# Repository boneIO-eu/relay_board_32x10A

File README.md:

# relay_board_32x10A
Realy Board 32x10A

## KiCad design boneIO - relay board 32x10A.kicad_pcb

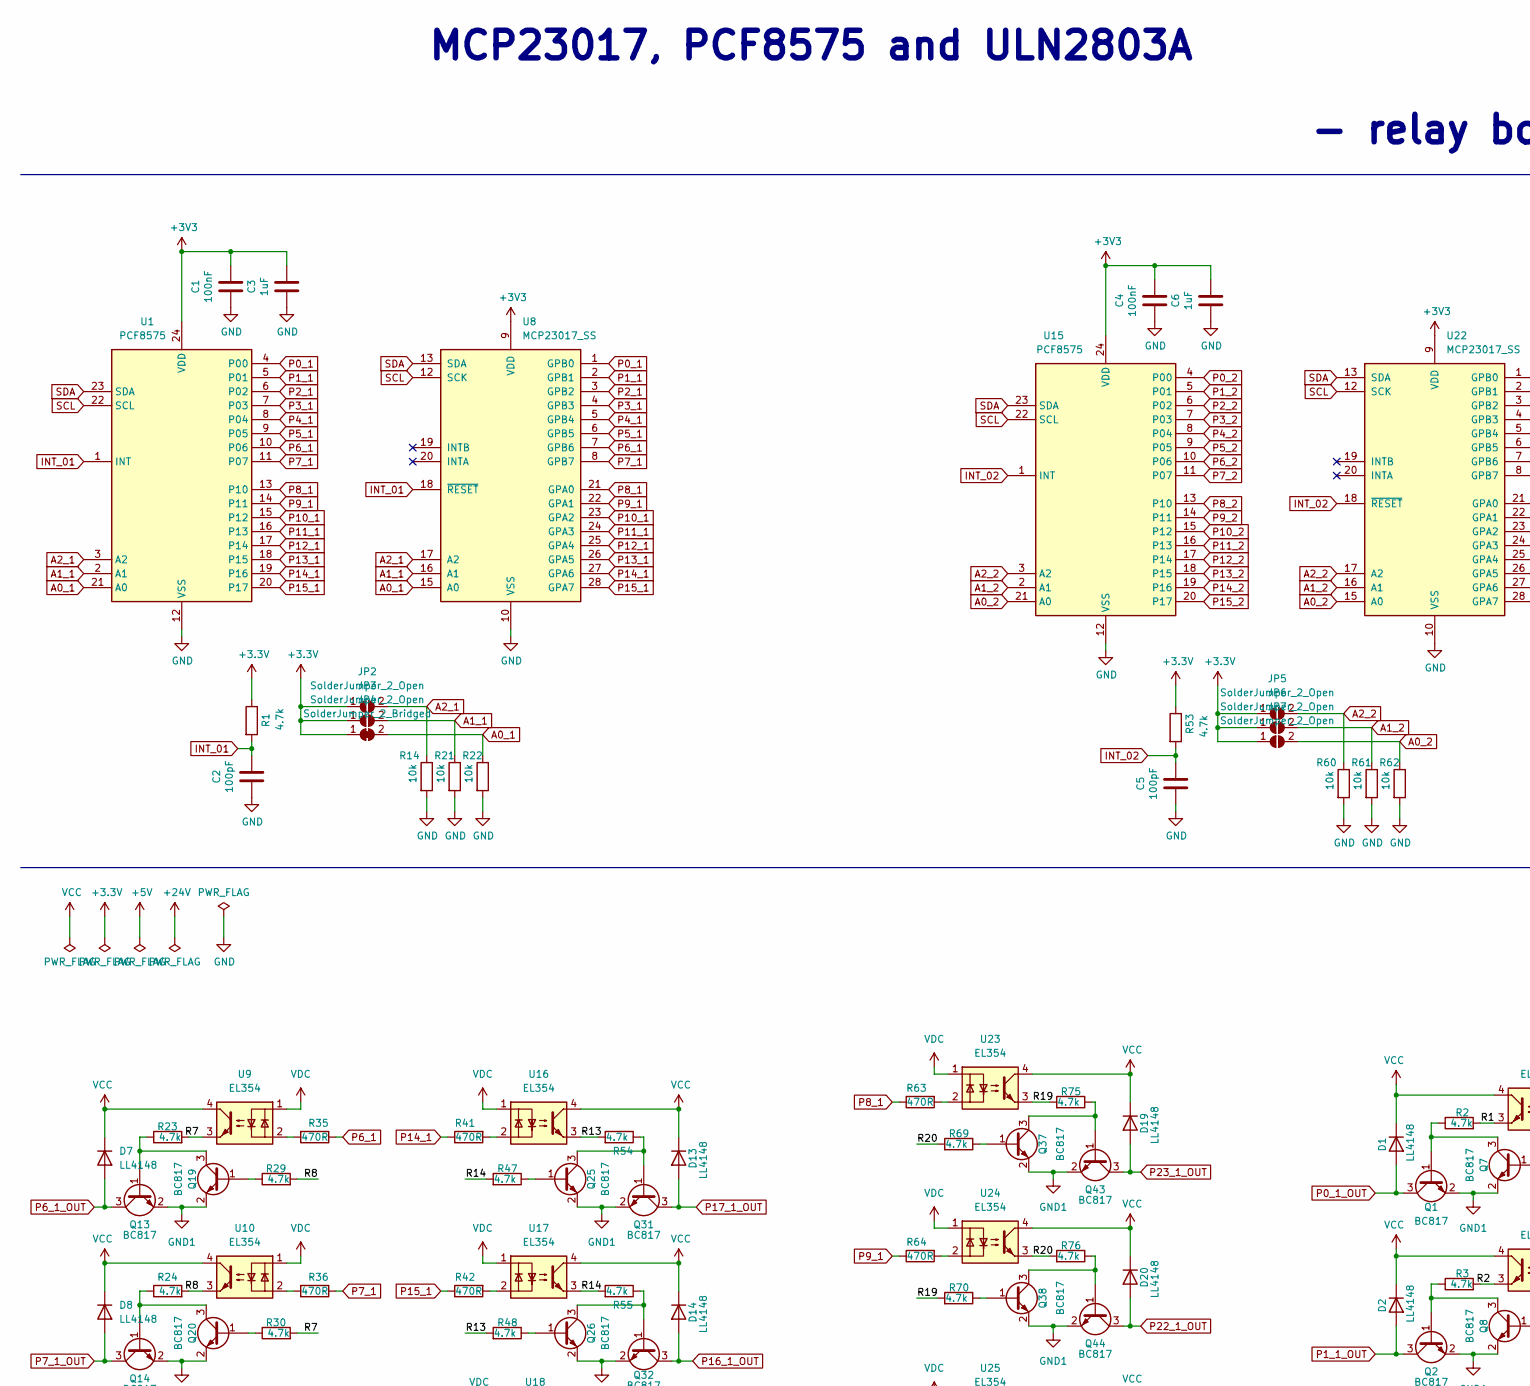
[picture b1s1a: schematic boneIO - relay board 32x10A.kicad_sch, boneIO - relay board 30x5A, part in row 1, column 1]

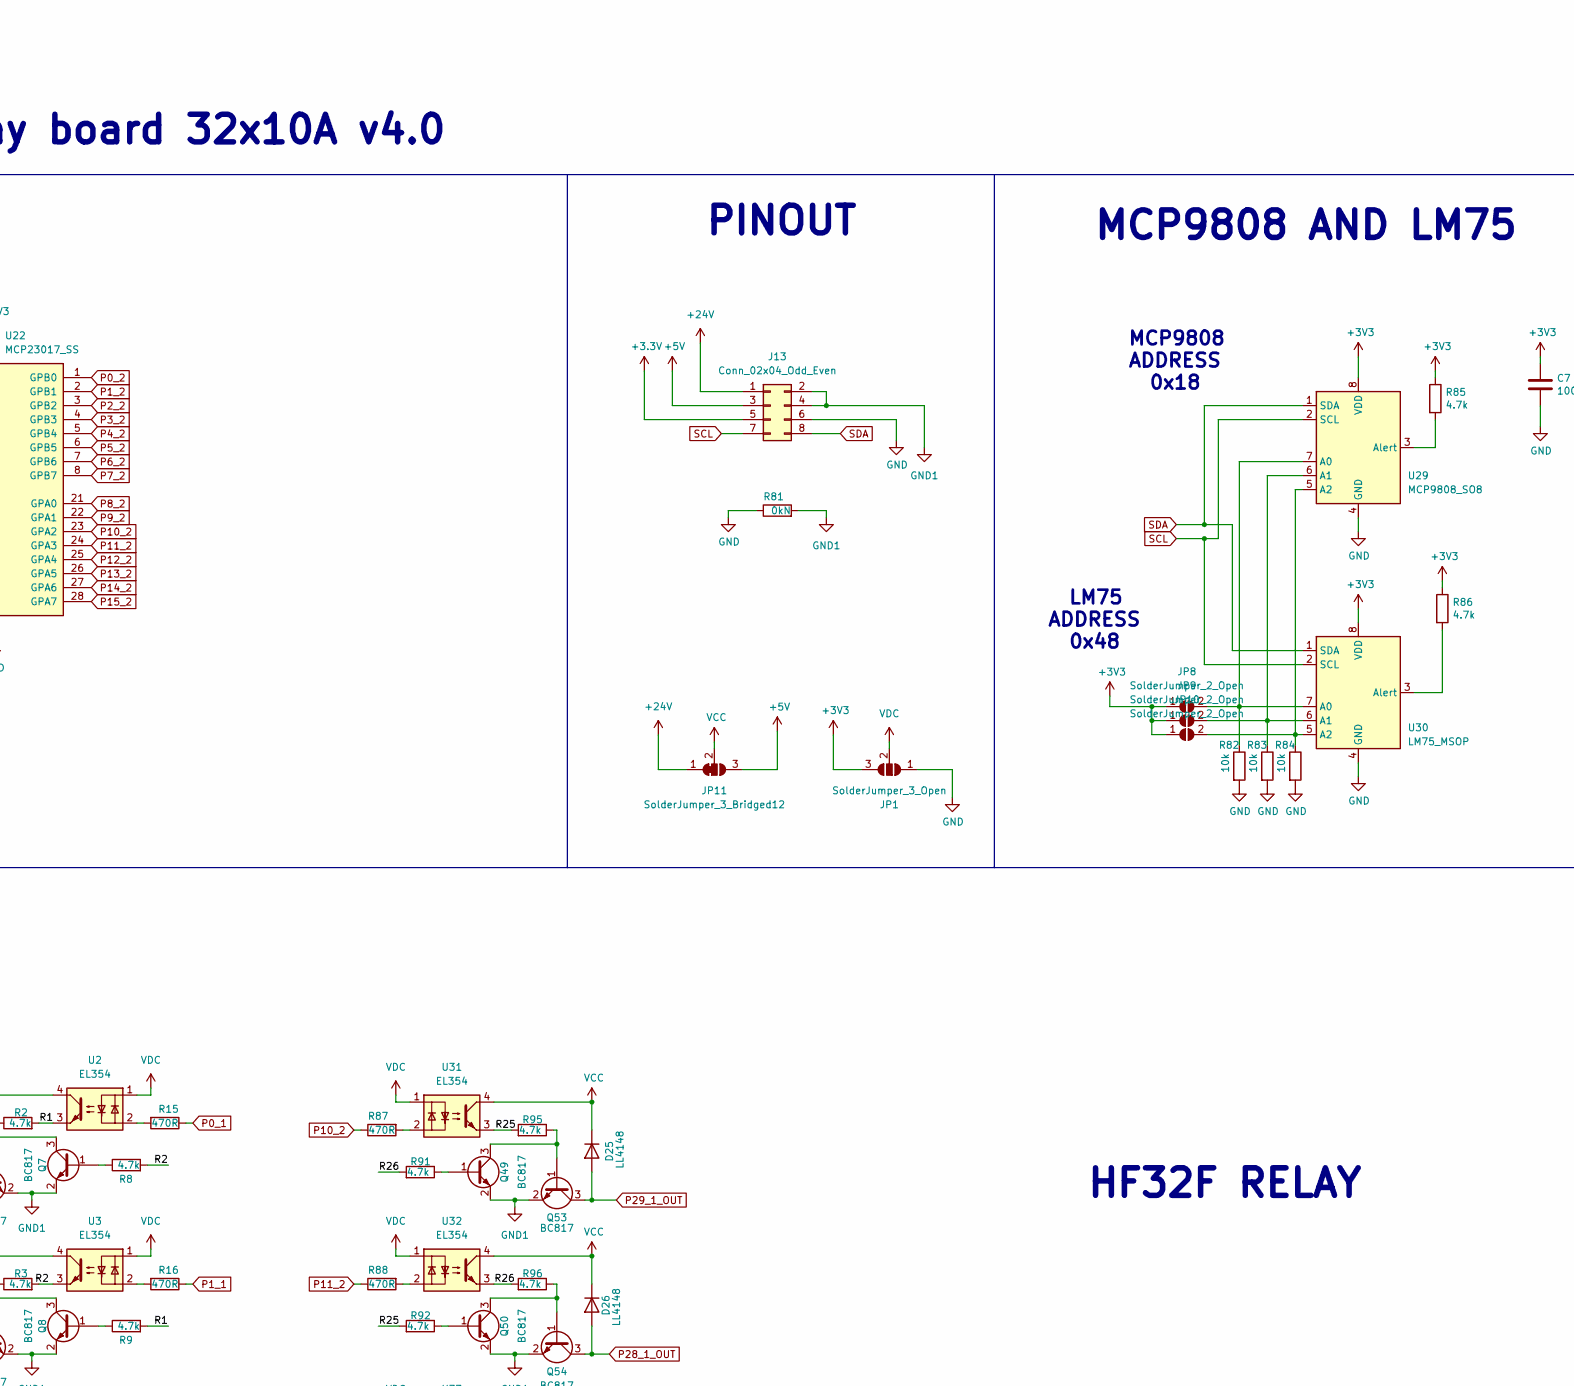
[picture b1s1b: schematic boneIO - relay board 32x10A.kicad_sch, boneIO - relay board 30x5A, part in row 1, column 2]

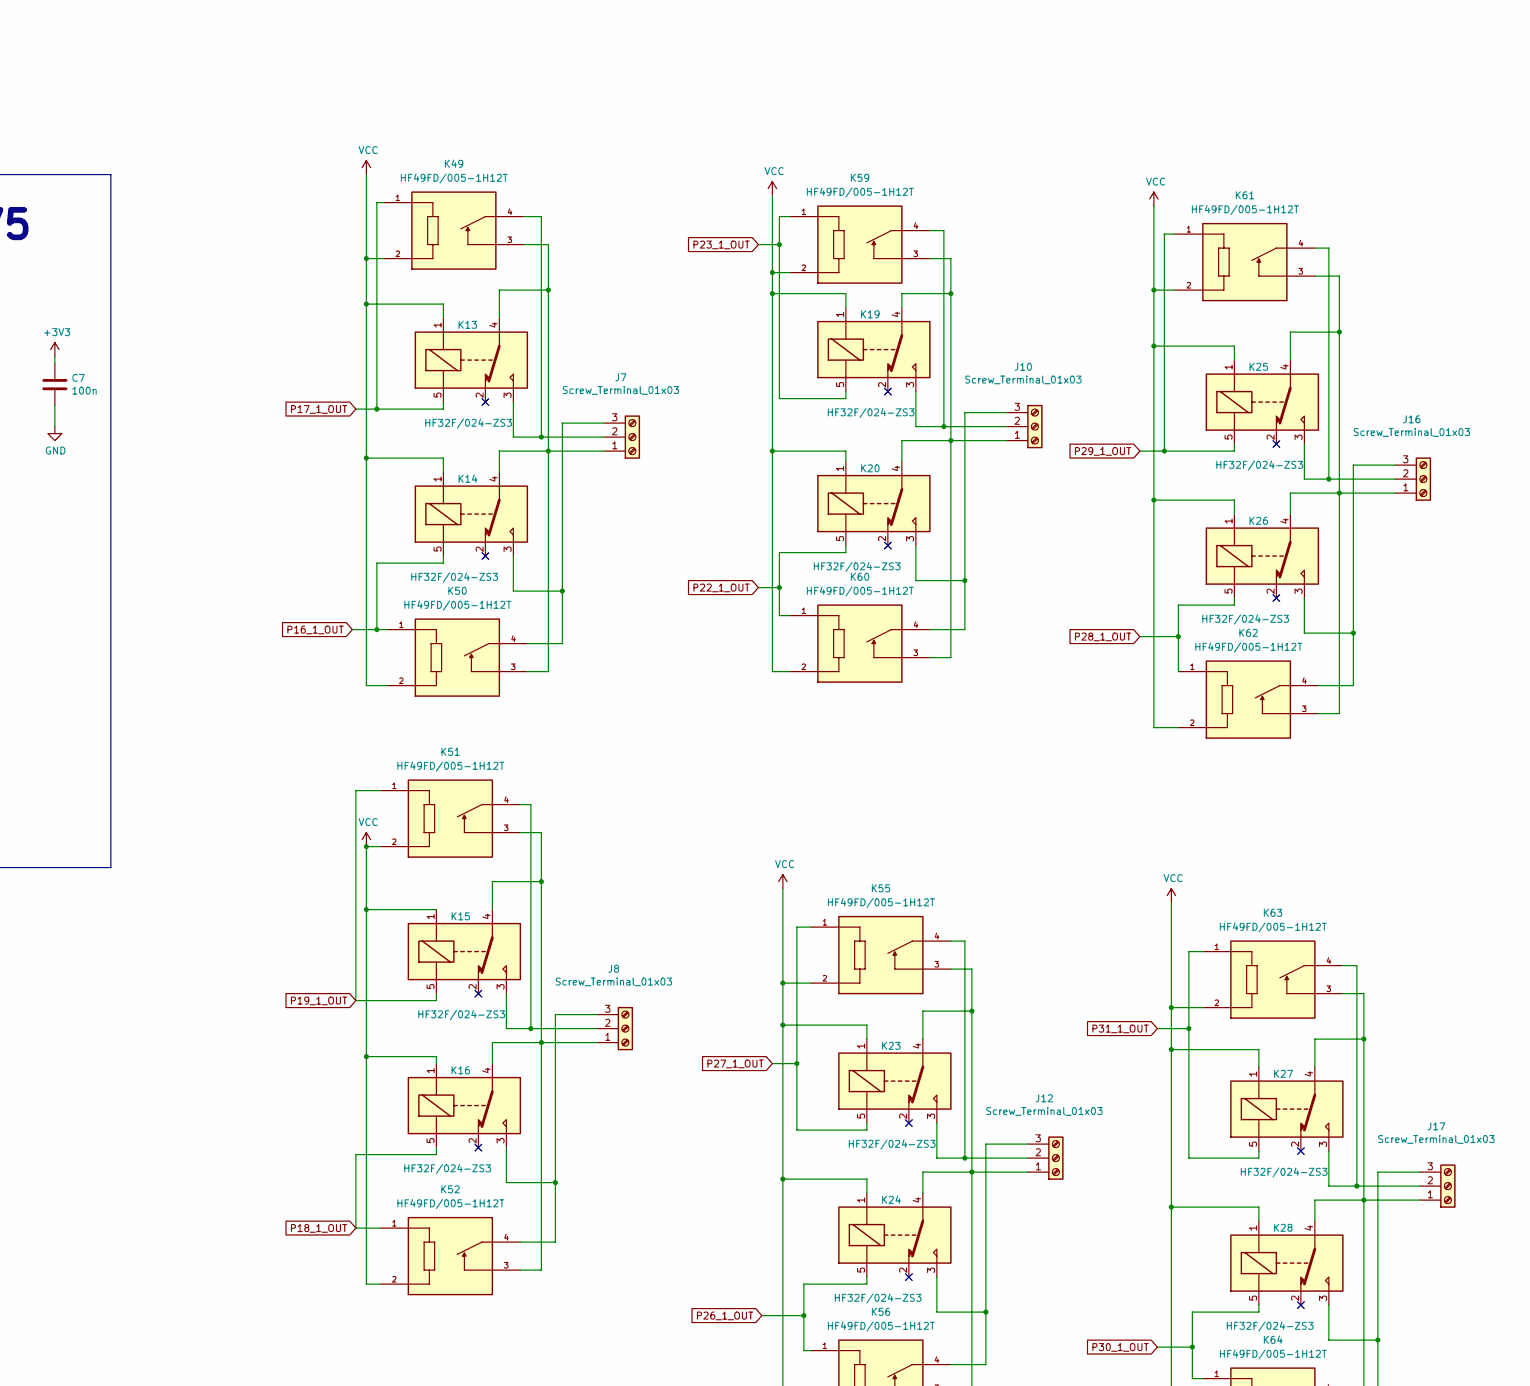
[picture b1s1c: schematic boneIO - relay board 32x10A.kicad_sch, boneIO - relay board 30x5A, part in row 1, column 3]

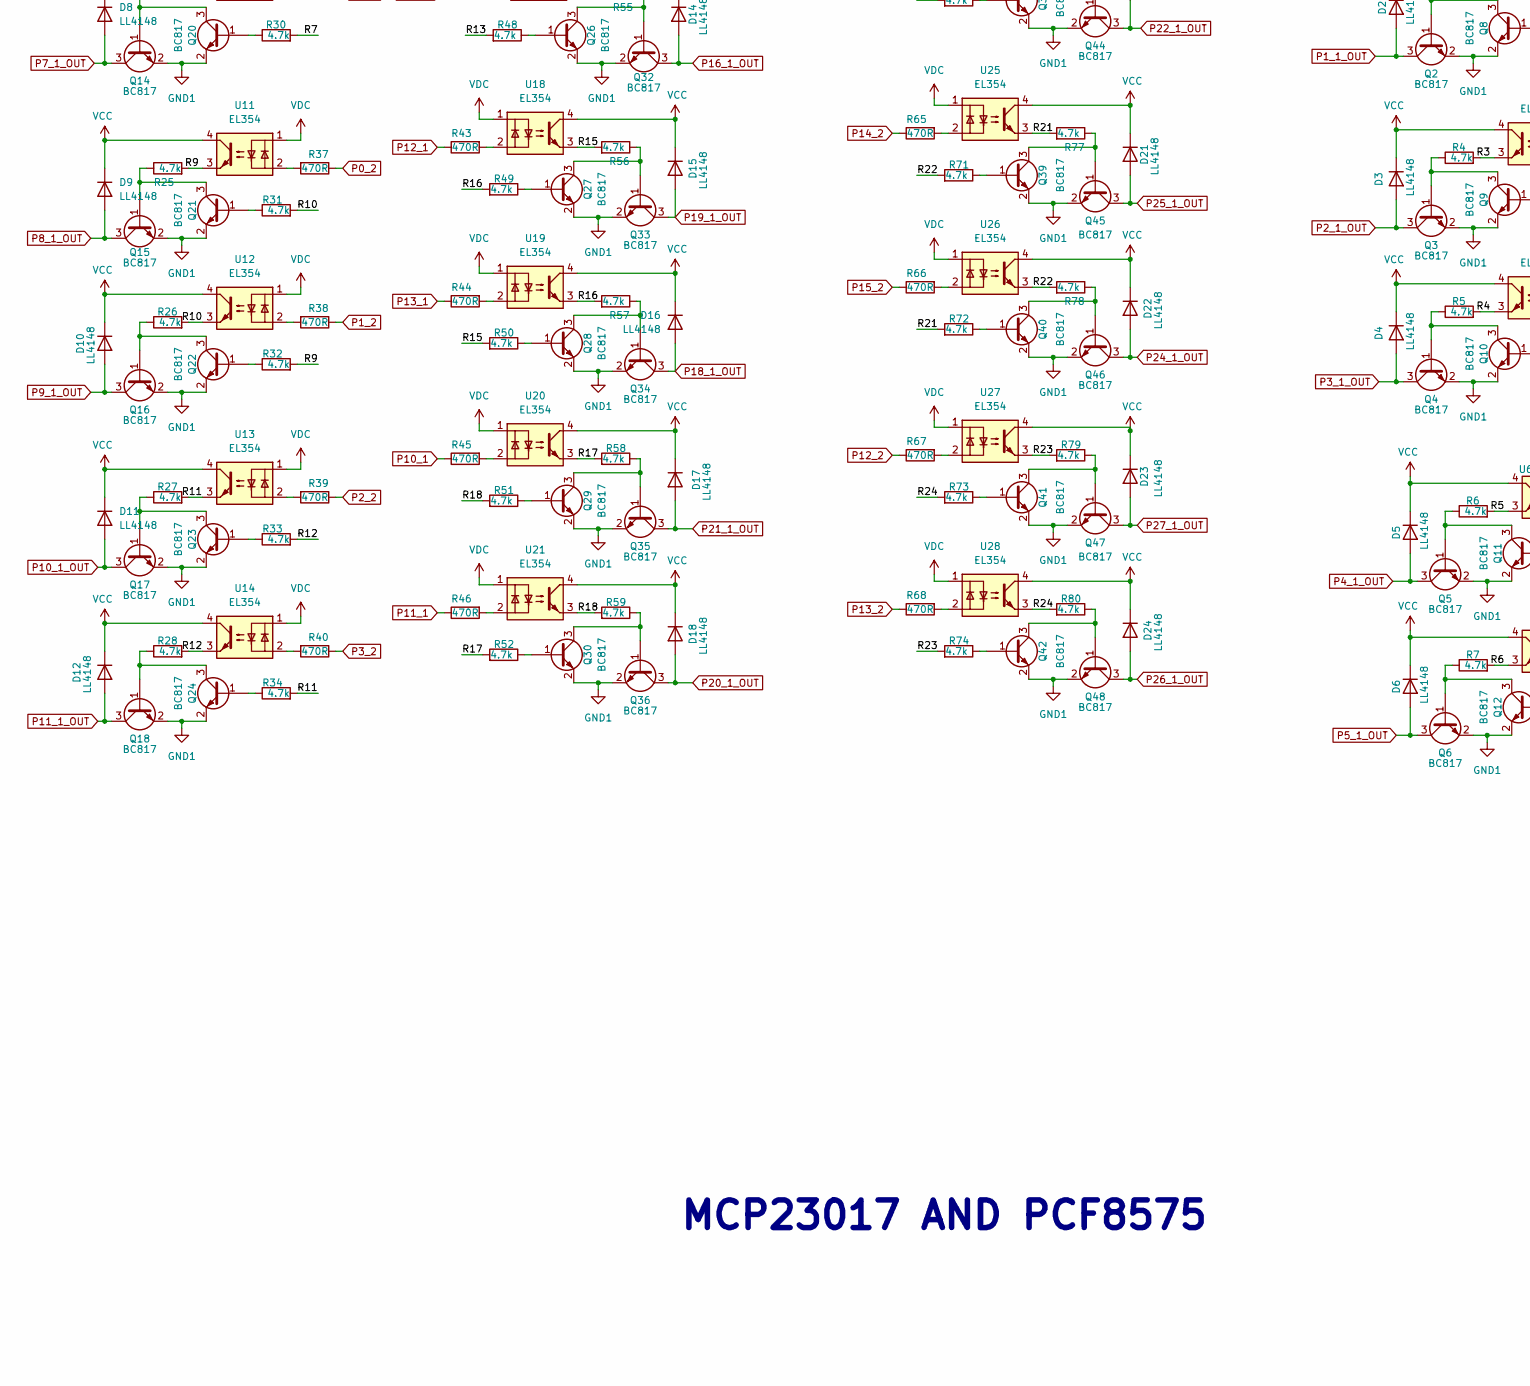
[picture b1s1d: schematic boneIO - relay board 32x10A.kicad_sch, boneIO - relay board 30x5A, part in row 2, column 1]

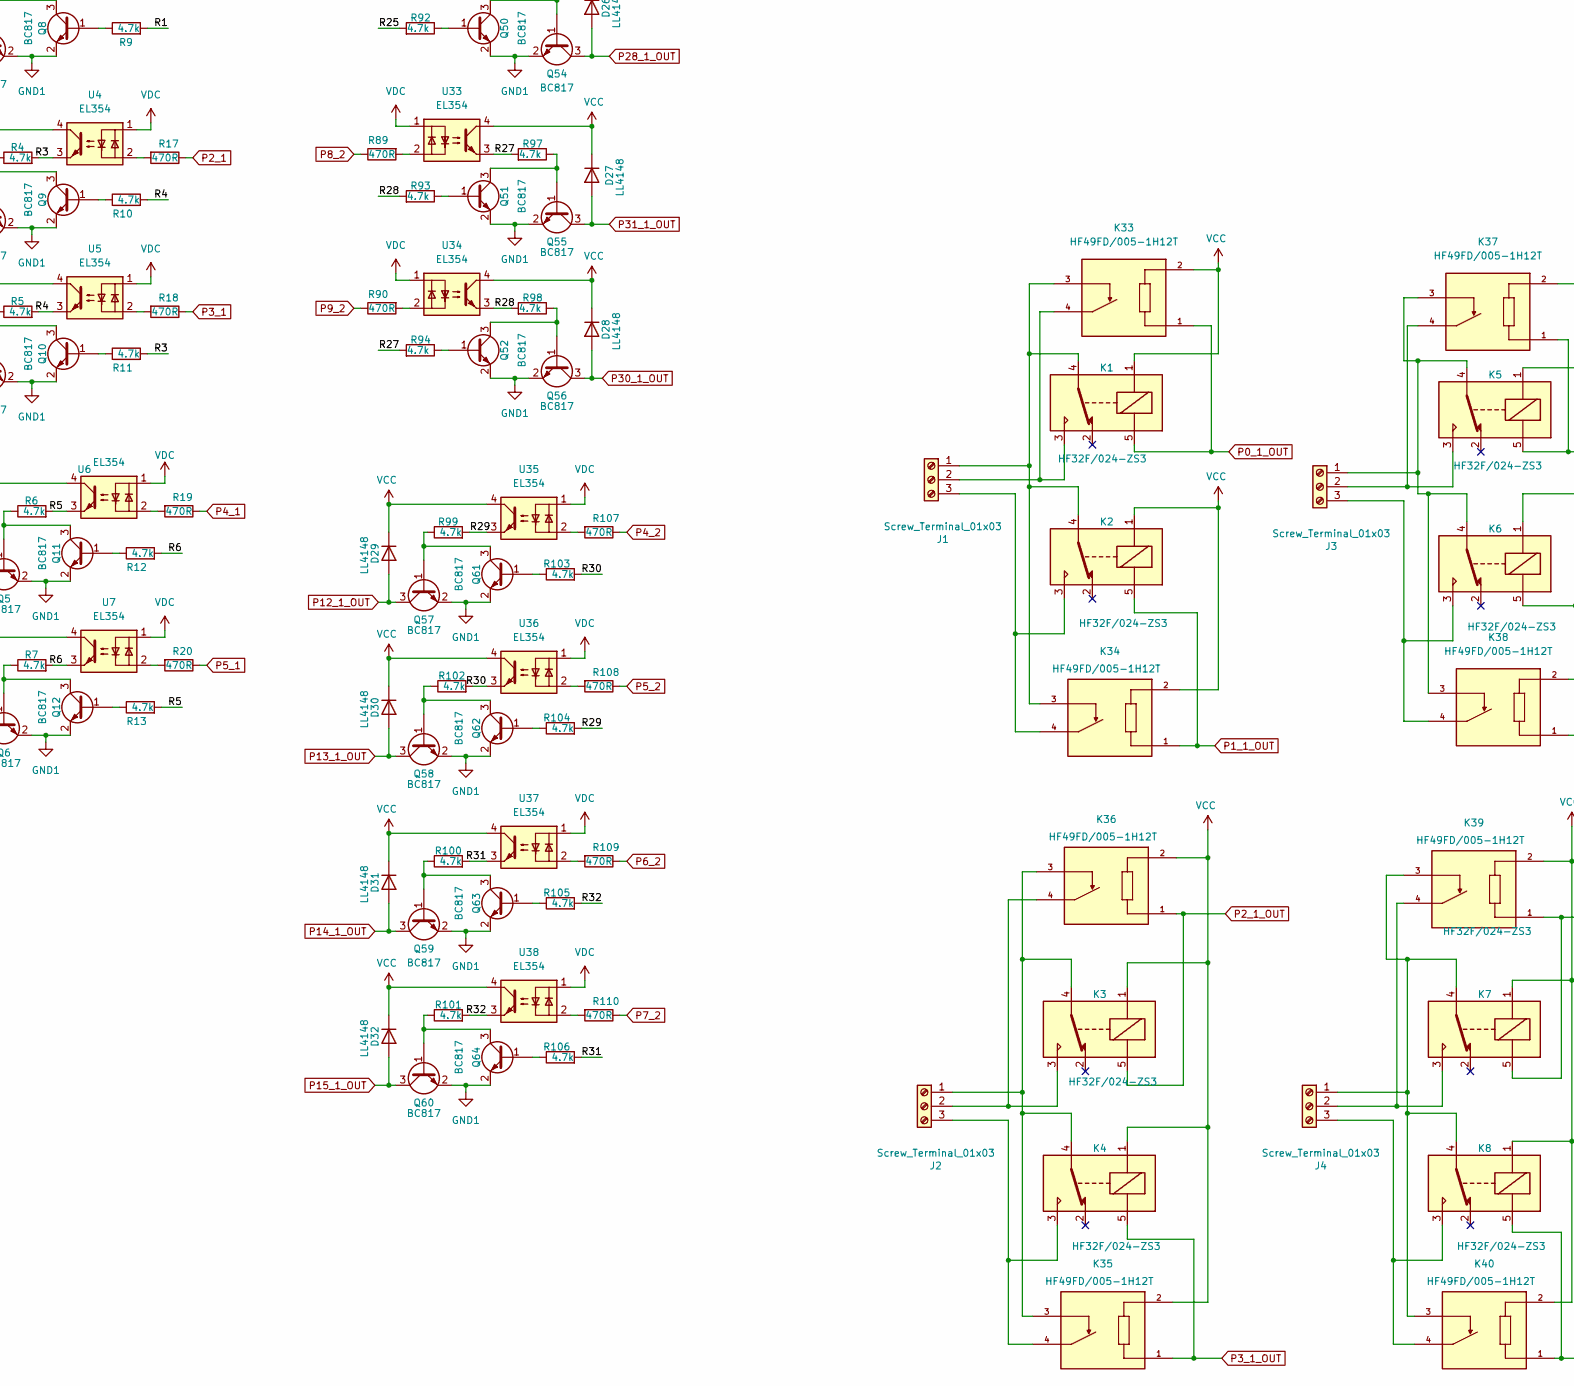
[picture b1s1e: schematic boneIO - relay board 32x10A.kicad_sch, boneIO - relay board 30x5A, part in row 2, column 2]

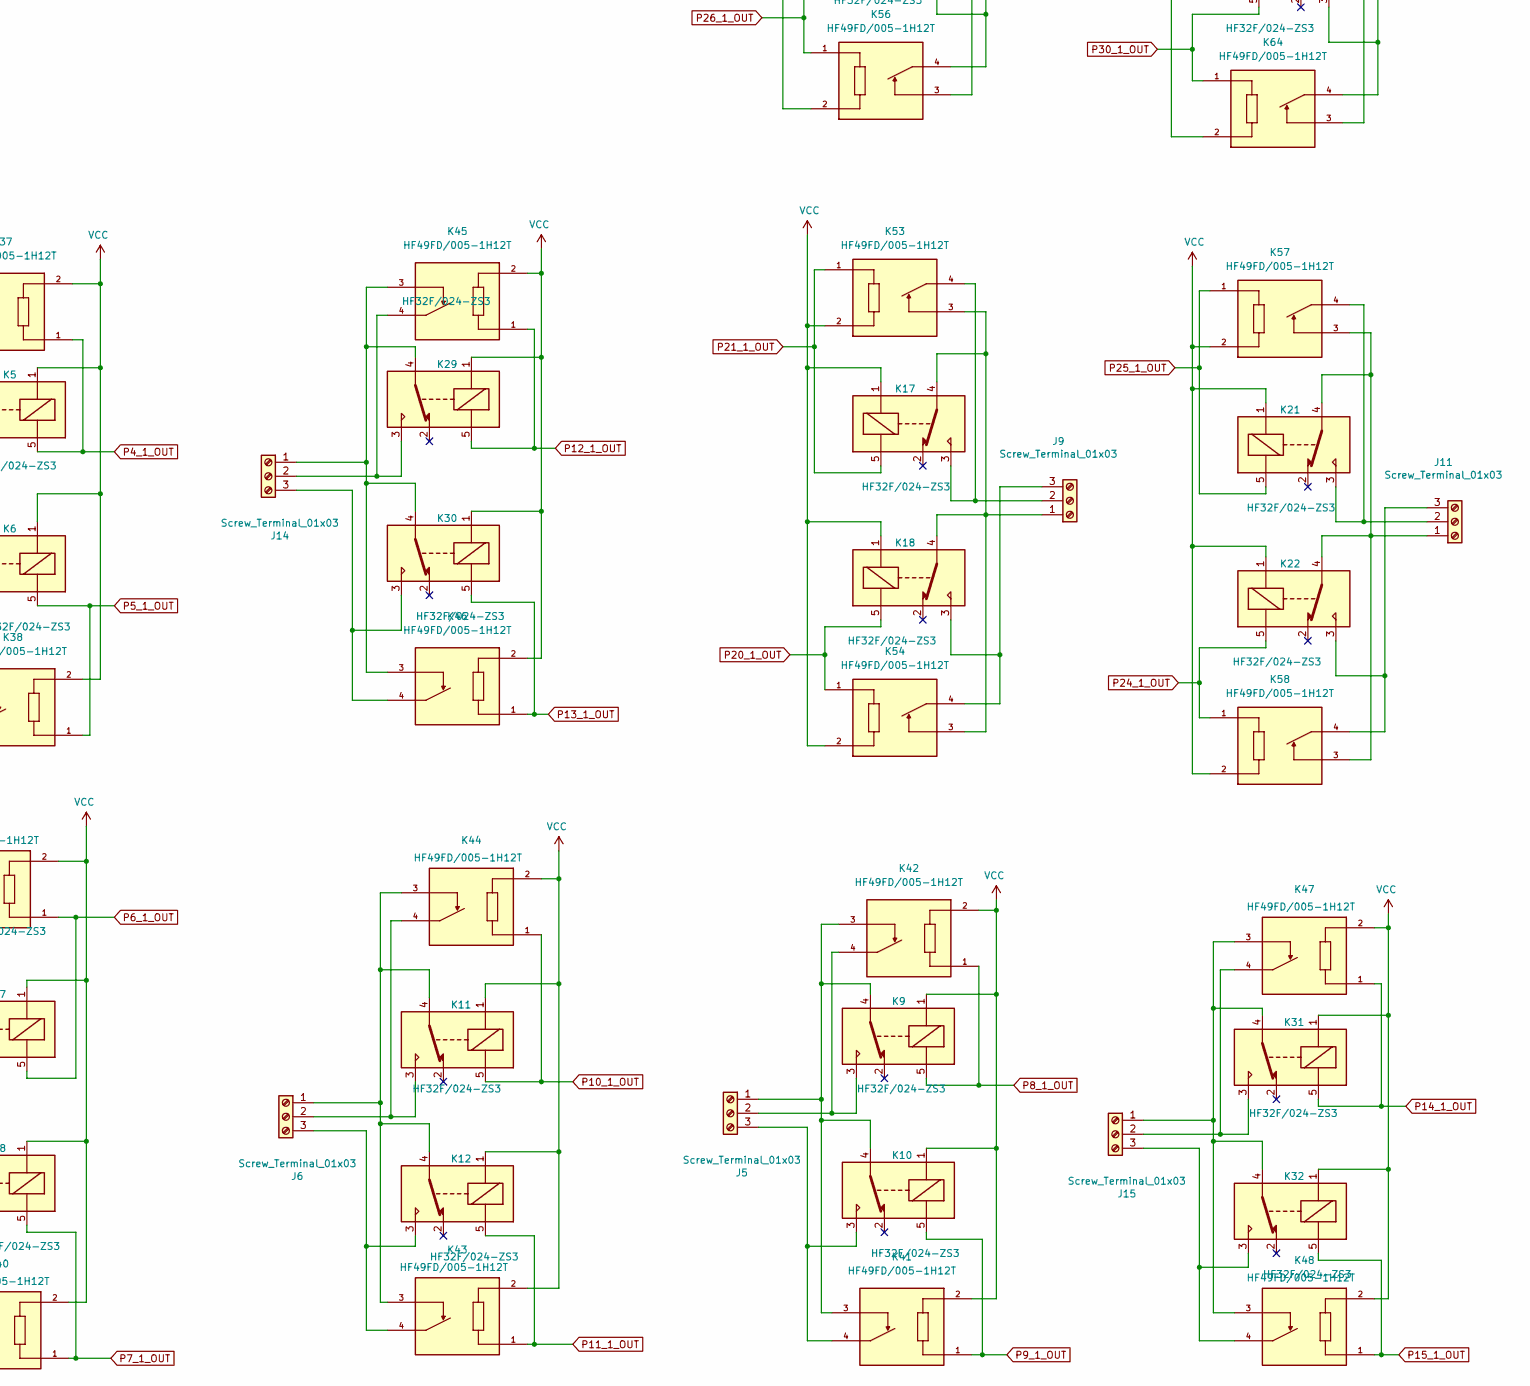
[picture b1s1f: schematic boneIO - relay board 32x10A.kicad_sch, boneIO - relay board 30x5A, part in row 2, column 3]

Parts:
C1, C4: 100nF; C_0603_1608Metric
C2, C5: 100pF; C_0603_1608Metric
C3, C6: 1uF; C_0603_1608Metric
C7: 100n; C_0603_1608Metric
D1, D2, D3, D4, D5, D6, D7, D8, D9, D10, D11, D12, D13, D14, D15, D16, D17, D18, D19, D20, D21, D22, D23, D24, D25, D26, D27, D28, D29, D30, D31, D32: LL4148; D_MiniMELF
J1, J2, J3, J4, J5, J6, J7, J8, J9, J10, J11, J12, J14, J15, J16, J17: Screw_Terminal_01x03; PhoenixContact_GMSTBA_2,5_3-G_1x03_P7.50mm_Horizontal
J13: Conn_02x04_Odd_Even; PinHeader_2x04_P2.54mm_Vertical
JP1: SolderJumper_3_Open; SolderJumper-3_P1.3mm_Open_RoundedPad1.0x1.5mm_NumberLabels
JP2, JP3, JP5, JP6, JP7, JP8, JP9, JP10: SolderJumper_2_Open; SolderJumper-2_P1.3mm_Open_RoundedPad1.0x1.5mm
JP4: SolderJumper_2_Bridged; SolderJumper-2_P1.3mm_Bridged_RoundedPad1.0x1.5mm
JP11: SolderJumper_3_Bridged12; SolderJumper-3_P1.3mm_Bridged2Bar12_RoundedPad1.0x1.5mm
K1, K2, K3, K4, K5, K6, K7, K8, K9, K10, K11, K12, K13, K14, K15, K16, K17, K18, K19, K20, K21, K22, K23, K24, K25, K26, K27, K28, K29, K30, K31, K32: HF32F/024-ZS3; Realy_DPST_HF32F
K33, K34, K35, K36, K37, K38, K39, K40, K41, K42, K43, K44, K45, K46, K47, K48, K49, K50, K51, K52, K53, K54, K55, K56, K57, K58, K59, K60, K61, K62, K63, K64: HF49FD/005-1H12T; RELAY_HF49FD_005-1H11T; PARTREV 1.13
Q1, Q2, Q3, Q4, Q5, Q6, Q7, Q8, Q9, Q10, Q11, Q12, Q13, Q14, Q15, Q16, Q17, Q18, Q19, Q20, Q21, Q22, Q23, Q24, Q25, Q26, Q27, Q28, Q29, Q30, Q31, Q32, Q33, Q34, Q35, Q36, Q37, Q38, Q39, Q40, Q41, Q42, Q43, Q44, Q45, Q46, Q47, Q48, Q49, Q50, Q51, Q52, Q53, Q54, Q55, Q56, Q57, Q58, Q59, Q60, Q61, Q62, Q63, Q64: BC817; SOT-23
R1, R2, R3, R4, R5, R6, R7, R8, R9, R10, R11, R12, R13, R23, R24, R25, R26, R27, R28, R29, R30, R31, R32, R33, R34, R47, R48, R49, R50, R51, R52, R53, R54, R55, R56, R57, R58, R59, R69, R70, R71, R72, R73, R74, R75, R76, R77, R78, R79, R80, R85, R86, R91, R92, R93, R94, R95, R96, R97, R98, R99, R100, R101, R102, R103, R104, R105, R106: 4.7k; R_0603_1608Metric
R14, R21, R22, R60, R61, R62, R82, R83, R84: 10k; R_0603_1608Metric
R15, R16, R17, R18, R19, R20, R35, R36, R37, R38, R39, R40, R41, R42, R43, R44, R45, R46, R63, R64, R65, R66, R67, R68, R87, R88, R89, R90, R107, R108, R109, R110: 470R; R_0603_1608Metric
R81: 0kN; R_0805_2012Metric
U1, U15: PCF8575; SSOP-24_5.3x8.2mm_P0.65mm
U2, U3, U4, U5, U6, U7, U9, U10, U11, U12, U13, U14, U16, U17, U18, U19, U20, U21, U23, U24, U25, U26, U27, U28, U31, U32, U33, U34, U35, U36, U37, U38: EL354; OPTO_EL357N-G
U8, U22: MCP23017_SS; SSOP-28_5.3x10.2mm_P0.65mm
U29: MCP9808_SO8; SO-8_3.9x4.9mm_P1.27mm
U30: LM75_MSOP; MSOP-8_3x3mm_P0.65mm

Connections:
+5V: J13.3, JP11.3 (B)
+24V: J13.1, JP11.1 (A)
/R1: R2.2, R9.2, U2.3
/R2: R3.2, R8.2, U3.3
/R3: R4.2, R11.2, U4.3
/R4: R5.2, R10.2, U5.3
/R5: R6.2, R13.2, U6.3
/R6: R7.2, R12.2, U7.3
/R7: R23.2, R30.2, U9.3
/R8: R24.2, R29.2, U10.3
/R9: R25.2, R32.2, U11.3
/R10: R26.2, R31.2, U12.3
/R11: R27.2, R34.2, U13.3
/R12: R28.2, R33.2, U14.3
/R13: R48.2, R54.2, U16.3
/R14: R47.2, R55.2, U17.3
/R15: R50.2, R56.2, U18.3
/R16: R49.2, R57.2, U19.3
/R17: R52.2, R58.2, U20.3
/R18: R51.2, R59.2, U21.3
/R19: R70.2, R75.2, U23.3
/R20: R69.2, R76.2, U24.3
/R21: R72.2, R77.2, U25.3
/R22: R71.2, R78.2, U26.3
/R23: R74.2, R79.2, U27.3
/R24: R73.2, R80.2, U28.3
/R25: R92.2, R95.2, U31.3
/R26: R91.2, R96.2, U32.3
/R27: R94.2, R97.2, U33.3
/R28: R93.2, R98.2, U34.3
/R29: R99.2, R104.2, U35.3
/R30: R102.2, R103.2, U36.3
/R31: R100.2, R106.2, U37.3
/R32: R101.2, R105.2, U38.3
A0_1: JP4.2 (B), R22.1, U1.21 (A0), U8.15 (A0)
A0_2: JP7.2 (B), R62.1, U15.21 (A0), U22.15 (A0)
A1_1: JP3.2 (B), R21.1, U1.2 (A1), U8.16 (A1)
A1_2: JP6.2 (B), R61.1, U15.2 (A1), U22.16 (A1)
A2_1: JP2.2 (B), R14.1, U1.3 (A2), U8.17 (A2)
A2_2: JP5.2 (B), R60.1, U15.3 (A2), U22.17 (A2)
GND: C1.2, C2.2, C3.2, C4.2, C5.2, C6.2, C7.2, J13.6, JP1.1 (A), R14.2, R21.2, R22.2, R60.2, R61.2, R62.2, R81.1, R82.2, R83.2, R84.2, U1.12 (VSS), U8.10 (VSS), U15.12 (VSS), U22.10 (VSS), U29.4 (GND), U30.4 (GND)
GND1: J13.2, J13.4, Q1.2 (E), Q2.2 (E), Q3.2 (E), Q4.2 (E), Q5.2 (E), Q6.2 (E), Q7.2 (E), Q8.2 (E), Q9.2 (E), Q10.2 (E), Q11.2 (E), Q12.2 (E), Q13.2 (E), Q14.2 (E), Q15.2 (E), Q16.2 (E), Q17.2 (E), Q18.2 (E), Q19.2 (E), Q20.2 (E), Q21.2 (E), Q22.2 (E), Q23.2 (E), Q24.2 (E), Q25.2 (E), Q26.2 (E), Q27.2 (E), Q28.2 (E), Q29.2 (E), Q30.2 (E), Q31.2 (E), Q32.2 (E), Q33.2 (E), Q34.2 (E), Q35.2 (E), Q36.2 (E), Q37.2 (E), Q38.2 (E), Q39.2 (E), Q40.2 (E), Q41.2 (E), Q42.2 (E), Q43.2 (E), Q44.2 (E), Q45.2 (E), Q46.2 (E), Q47.2 (E), Q48.2 (E), Q49.2 (E), Q50.2 (E), Q51.2 (E), Q52.2 (E), Q53.2 (E), Q54.2 (E), Q55.2 (E), Q56.2 (E), Q57.2 (E), Q58.2 (E), Q59.2 (E), Q60.2 (E), Q61.2 (E), Q62.2 (E), Q63.2 (E), Q64.2 (E), R81.2
INT_01: C2.1, R1.2, U1.1 (INT), U8.18 (~RESET)
INT_02: C5.1, R53.2, U15.1 (INT), U22.18 (~RESET)
unnamed: J1.1, K1.4, K2.4, K33.3, K34.3
unnamed: J1.2, K1.3, K33.4
unnamed: J1.3, K2.3, K34.4
unnamed: J2.1, K3.4, K4.4, K35.3, K36.3
unnamed: J2.2, K3.3, K36.4
unnamed: J2.3, K4.3, K35.4
unnamed: J3.1, K5.4, K6.4, K37.3, K38.3
unnamed: J3.2, K5.3, K37.4
unnamed: J3.3, K6.3, K38.4
unnamed: J4.1, K7.4, K8.4, K39.3, K40.3
unnamed: J4.2, K7.3, K39.4
unnamed: J4.3, K8.3, K40.4
unnamed: J5.1, K9.4, K10.4, K41.3, K42.3
unnamed: J5.2, K9.3, K42.4
unnamed: J5.3, K10.3, K41.4
unnamed: J6.1, K11.4, K12.4, K43.3, K44.3
unnamed: J6.2, K11.3, K44.4
unnamed: J6.3, K12.3, K43.4
unnamed: J7.1, K13.4, K14.4, K49.3, K50.3
unnamed: J7.2, K13.3, K49.4
unnamed: J7.3, K14.3, K50.4
unnamed: J8.1, K15.4, K16.4, K51.3, K52.3
unnamed: J8.2, K15.3, K51.4
unnamed: J8.3, K16.3, K52.4
unnamed: J9.1, K17.4, K18.4, K53.3, K54.3
unnamed: J9.2, K17.3, K53.4
unnamed: J9.3, K18.3, K54.4
unnamed: J10.1, K19.4, K20.4, K59.3, K60.3
unnamed: J10.2, K19.3, K59.4
unnamed: J10.3, K20.3, K60.4
unnamed: J11.1, K21.4, K22.4, K57.3, K58.3
unnamed: J11.2, K21.3, K57.4
unnamed: J11.3, K22.3, K58.4
unnamed: J12.1, K23.4, K24.4, K55.3, K56.3
unnamed: J12.3, K24.3, K56.4
unnamed: J14.1, K29.4, K30.4, K45.3, K46.3
unnamed: J14.2, K29.3, K45.4
unnamed: J14.3, K30.3, K46.4
unnamed: J15.1, K31.4, K32.4, K47.3, K48.3
unnamed: J15.2, K31.3, K47.4
unnamed: J15.3, K32.3, K48.4
unnamed: J16.1, K25.4, K26.4, K61.3, K62.3
unnamed: J16.2, K25.3, K61.4
unnamed: J16.3, K26.3, K62.4
unnamed: J17.1, K27.4, K28.4, K63.3, K64.3
unnamed: J17.2, K27.3, K63.4
unnamed: J17.3, K28.3, K64.4
unnamed: JP8.2 (B), R82.1, U29.7 (A0), U30.7 (A0)
unnamed: JP9.2 (B), R83.1, U29.6 (A1), U30.6 (A1)
unnamed: JP10.2 (B), R84.1, U29.5 (A2), U30.5 (A2)
unnamed: J12.2, K23.3, K55.4
unnamed: Q1.1 (B), Q7.3 (C), R2.1
unnamed: Q2.1 (B), Q8.3 (C), R3.1
unnamed: Q3.1 (B), Q9.3 (C), R4.1
unnamed: Q7.1 (B), R8.1
unnamed: Q8.1 (B), R9.1
unnamed: Q9.1 (B), R10.1
unnamed: Q10.1 (B), R11.1
unnamed: Q4.1 (B), Q10.3 (C), R5.1
unnamed: Q11.1 (B), R12.1
unnamed: Q5.1 (B), Q11.3 (C), R6.1
unnamed: Q12.1 (B), R13.1
unnamed: Q6.1 (B), Q12.3 (C), R7.1
unnamed: Q13.1 (B), Q19.3 (C), R23.1
unnamed: Q14.1 (B), Q20.3 (C), R24.1
unnamed: Q15.1 (B), Q21.3 (C), R25.1
unnamed: Q16.1 (B), Q22.3 (C), R26.1
unnamed: Q17.1 (B), Q23.3 (C), R27.1
unnamed: Q18.1 (B), Q24.3 (C), R28.1
unnamed: Q19.1 (B), R29.1
unnamed: Q20.1 (B), R30.1
unnamed: Q21.1 (B), R31.1
unnamed: Q22.1 (B), R32.1
unnamed: Q23.1 (B), R33.1
unnamed: Q24.1 (B), R34.1
unnamed: Q25.1 (B), R47.1
unnamed: Q25.3 (C), Q31.1 (B), R54.1
unnamed: Q26.1 (B), R48.1
unnamed: Q26.3 (C), Q32.1 (B), R55.1
unnamed: Q27.1 (B), R49.1
unnamed: Q27.3 (C), Q33.1 (B), R56.1
unnamed: Q28.1 (B), R50.1
unnamed: Q28.3 (C), Q34.1 (B), R57.1
unnamed: Q29.1 (B), R51.1
unnamed: Q29.3 (C), Q35.1 (B), R58.1
unnamed: Q30.1 (B), R52.1
unnamed: Q30.3 (C), Q36.1 (B), R59.1
unnamed: Q37.1 (B), R69.1
unnamed: Q37.3 (C), Q43.1 (B), R75.1
unnamed: Q38.1 (B), R70.1
unnamed: Q38.3 (C), Q44.1 (B), R76.1
unnamed: Q39.1 (B), R71.1
unnamed: Q39.3 (C), Q45.1 (B), R77.1
unnamed: Q40.1 (B), R72.1
unnamed: Q40.3 (C), Q46.1 (B), R78.1
unnamed: Q41.1 (B), R73.1
unnamed: Q41.3 (C), Q47.1 (B), R79.1
unnamed: Q42.1 (B), R74.1
unnamed: Q42.3 (C), Q48.1 (B), R80.1
unnamed: Q49.1 (B), R91.1
unnamed: Q49.3 (C), Q53.1 (B), R95.1
unnamed: Q50.1 (B), R92.1
unnamed: Q50.3 (C), Q54.1 (B), R96.1
unnamed: Q51.1 (B), R93.1
unnamed: Q51.3 (C), Q55.1 (B), R97.1
unnamed: Q52.1 (B), R94.1
unnamed: Q52.3 (C), Q56.1 (B), R98.1
unnamed: Q57.1 (B), Q61.3 (C), R99.1
unnamed: Q58.1 (B), Q62.3 (C), R102.1
unnamed: Q59.1 (B), Q63.3 (C), R100.1
unnamed: Q60.1 (B), Q64.3 (C), R101.1
unnamed: Q61.1 (B), R103.1
unnamed: Q62.1 (B), R104.1
unnamed: Q63.1 (B), R105.1
unnamed: Q64.1 (B), R106.1
unnamed: R15.2, U2.2
unnamed: R16.2, U3.2
unnamed: R17.2, U4.2
unnamed: R18.2, U5.2
unnamed: R19.2, U6.2
unnamed: R20.2, U7.2
unnamed: R35.2, U9.2
unnamed: R36.2, U10.2
unnamed: R37.2, U11.2
unnamed: R38.2, U12.2
unnamed: R39.2, U13.2
unnamed: R40.2, U14.2
unnamed: R41.2, U16.2
unnamed: R42.2, U17.2
unnamed: R43.2, U18.2
unnamed: R44.2, U19.2
unnamed: R45.2, U20.2
unnamed: R46.2, U21.2
unnamed: R63.2, U23.2
unnamed: R64.2, U24.2
unnamed: R65.2, U25.2
unnamed: R66.2, U26.2
unnamed: R67.2, U27.2
unnamed: R68.2, U28.2
unnamed: R85.2, U29.3 (Alert)
unnamed: R86.2, U30.3 (Alert)
unnamed: R87.2, U31.2
unnamed: R88.2, U32.2
unnamed: R89.2, U33.2
unnamed: R90.2, U34.2
unnamed: R107.2, U35.2
unnamed: R108.2, U36.2
unnamed: R109.2, U37.2
unnamed: R110.2, U38.2
P0_1: R15.1, U1.4 (P00), U8.1 (GPB0)
P0_1_OUT: D1.2 (A), K1.5, K33.1, Q1.3 (C)
P0_2: R37.1, U15.4 (P00), U22.1 (GPB0)
P1_1: R16.1, U1.5 (P01), U8.2 (GPB1)
P1_1_OUT: D2.2 (A), K2.5, K34.1, Q2.3 (C)
P1_2: R38.1, U15.5 (P01), U22.2 (GPB1)
P2_1: R17.1, U1.6 (P02), U8.3 (GPB2)
P2_1_OUT: D3.2 (A), K3.5, K36.1, Q3.3 (C)
P2_2: R39.1, U15.6 (P02), U22.3 (GPB2)
P3_1: R18.1, U1.7 (P03), U8.4 (GPB3)
P3_1_OUT: D4.2 (A), K4.5, K35.1, Q4.3 (C)
P3_2: R40.1, U15.7 (P03), U22.4 (GPB3)
P4_1: R19.1, U1.8 (P04), U8.5 (GPB4)
P4_1_OUT: D5.2 (A), K5.5, K37.1, Q5.3 (C)
P4_2: R107.1, U15.8 (P04), U22.5 (GPB4)
P5_1: R20.1, U1.9 (P05), U8.6 (GPB5)
P5_1_OUT: D6.2 (A), K6.5, K38.1, Q6.3 (C)
P5_2: R108.1, U15.9 (P05), U22.6 (GPB5)
P6_1: R35.1, U1.10 (P06), U8.7 (GPB6)
P6_1_OUT: D7.2 (A), K7.5, K39.1, Q13.3 (C)
P6_2: R109.1, U15.10 (P06), U22.7 (GPB6)
P7_1: R36.1, U1.11 (P07), U8.8 (GPB7)
P7_1_OUT: D8.2 (A), K8.5, K40.1, Q14.3 (C)
P7_2: R110.1, U15.11 (P07), U22.8 (GPB7)
P8_1: R63.1, U1.13 (P10), U8.21 (GPA0)
P8_1_OUT: D9.2 (A), K9.5, K42.1, Q15.3 (C)
P8_2: R89.1, U15.13 (P10), U22.21 (GPA0)
P9_1: R64.1, U1.14 (P11), U8.22 (GPA1)
P9_1_OUT: D10.2 (A), K10.5, K41.1, Q16.3 (C)
P9_2: R90.1, U15.14 (P11), U22.22 (GPA1)
P10_1: R45.1, U1.15 (P12), U8.23 (GPA2)
P10_1_OUT: D11.2 (A), K11.5, K44.1, Q17.3 (C)
P10_2: R87.1, U15.15 (P12), U22.23 (GPA2)
P11_1: R46.1, U1.16 (P13), U8.24 (GPA3)
P11_1_OUT: D12.2 (A), K12.5, K43.1, Q18.3 (C)
P11_2: R88.1, U15.16 (P13), U22.24 (GPA3)
P12_1: R43.1, U1.17 (P14), U8.25 (GPA4)
P12_1_OUT: D29.2 (A), K29.5, K45.1, Q57.3 (C)
P12_2: R67.1, U15.17 (P14), U22.25 (GPA4)
P13_1: R44.1, U1.18 (P15), U8.26 (GPA5)
P13_1_OUT: D30.2 (A), K30.5, K46.1, Q58.3 (C)
P13_2: R68.1, U15.18 (P15), U22.26 (GPA5)
P14_1: R41.1, U1.19 (P16), U8.27 (GPA6)
P14_1_OUT: D31.2 (A), K31.5, K47.1, Q59.3 (C)
P14_2: R65.1, U15.19 (P16), U22.27 (GPA6)
P15_1: R42.1, U1.20 (P17), U8.28 (GPA7)
P15_1_OUT: D32.2 (A), K32.5, K48.1, Q60.3 (C)
P15_2: R66.1, U15.20 (P17), U22.28 (GPA7)
P16_1_OUT: D14.2 (A), K14.5, K50.1, Q32.3 (C)
P17_1_OUT: D13.2 (A), K13.5, K49.1, Q31.3 (C)
P18_1_OUT: D16.2 (A), K16.5, K52.1, Q34.3 (C)
P19_1_OUT: D15.2 (A), K15.5, K51.1, Q33.3 (C)
P20_1_OUT: D18.2 (A), K18.5, K54.1, Q36.3 (C)
P21_1_OUT: D17.2 (A), K17.5, K53.1, Q35.3 (C)
P22_1_OUT: D20.2 (A), K20.5, K60.1, Q44.3 (C)
P23_1_OUT: D19.2 (A), K19.5, K59.1, Q43.3 (C)
P24_1_OUT: D22.2 (A), K22.5, K58.1, Q46.3 (C)
P25_1_OUT: D21.2 (A), K21.5, K57.1, Q45.3 (C)
P26_1_OUT: D24.2 (A), K24.5, K56.1, Q48.3 (C)
P27_1_OUT: D23.2 (A), K23.5, K55.1, Q47.3 (C)
P28_1_OUT: D26.2 (A), K26.5, K62.1, Q54.3 (C)
P29_1_OUT: D25.2 (A), K25.5, K61.1, Q53.3 (C)
P30_1_OUT: D28.2 (A), K28.5, K64.1, Q56.3 (C)
P31_1_OUT: D27.2 (A), K27.5, K63.1, Q55.3 (C)
SCL: J13.7, U1.22 (SCL), U8.12 (SCK), U15.22 (SCL), U22.12 (SCK), U29.2 (SCL), U30.2 (SCL)
SDA: J13.8, U1.23 (SDA), U8.13 (SDA), U15.23 (SDA), U22.13 (SDA), U29.1 (SDA), U30.1 (SDA)
VCC: D1.1 (K), D2.1 (K), D3.1 (K), D4.1 (K), D5.1 (K), D6.1 (K), D7.1 (K), D8.1 (K), D9.1 (K), D10.1 (K), D11.1 (K), D12.1 (K), D13.1 (K), D14.1 (K), D15.1 (K), D16.1 (K), D17.1 (K), D18.1 (K), D19.1 (K), D20.1 (K), D21.1 (K), D22.1 (K), D23.1 (K), D24.1 (K), D25.1 (K), D26.1 (K), D27.1 (K), D28.1 (K), D29.1 (K), D30.1 (K), D31.1 (K), D32.1 (K), JP11.2 (C), K1.1, K2.1, K3.1, K4.1, K5.1, K6.1, K7.1, K8.1, K9.1, K10.1, K11.1, K12.1, K13.1, K14.1, K15.1, K16.1, K17.1, K18.1, K19.1, K20.1, K21.1, K22.1, K23.1, K24.1, K25.1, K26.1, K27.1, K28.1, K29.1, K30.1, K31.1, K32.1, K33.2, K34.2, K35.2, K36.2, K37.2, K38.2, K39.2, K40.2, K41.2, K42.2, K43.2, K44.2, K45.2, K46.2, K47.2, K48.2, K49.2, K50.2, K51.2, K52.2, K53.2, K54.2, K55.2, K56.2, K57.2, K58.2, K59.2, K60.2, K61.2, K62.2, K63.2, K64.2, U2.4, U3.4, U4.4, U5.4, U6.4, U7.4, U9.4, U10.4, U11.4, U12.4, U13.4, U14.4, U16.4, U17.4, U18.4, U19.4, U20.4, U21.4, U23.4, U24.4, U25.4, U26.4, U27.4, U28.4, U31.4, U32.4, U33.4, U34.4, U35.4, U36.4, U37.4, U38.4
VDC: JP1.2 (C), U2.1, U3.1, U4.1, U5.1, U6.1, U7.1, U9.1, U10.1, U11.1, U12.1, U13.1, U14.1, U16.1, U17.1, U18.1, U19.1, U20.1, U21.1, U23.1, U24.1, U25.1, U26.1, U27.1, U28.1, U31.1, U32.1, U33.1, U34.1, U35.1, U36.1, U37.1, U38.1

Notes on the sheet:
PINOUT
MCP23017, PCF8575 and ULN2803A
LM75 ADDRESS 0x48
MCP23017 AND PCF8575
HF32F RELAY
MCP9808 AND LM75
- relay board 32x10A v4.0
MCP9808 ADDRESS 0x18

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
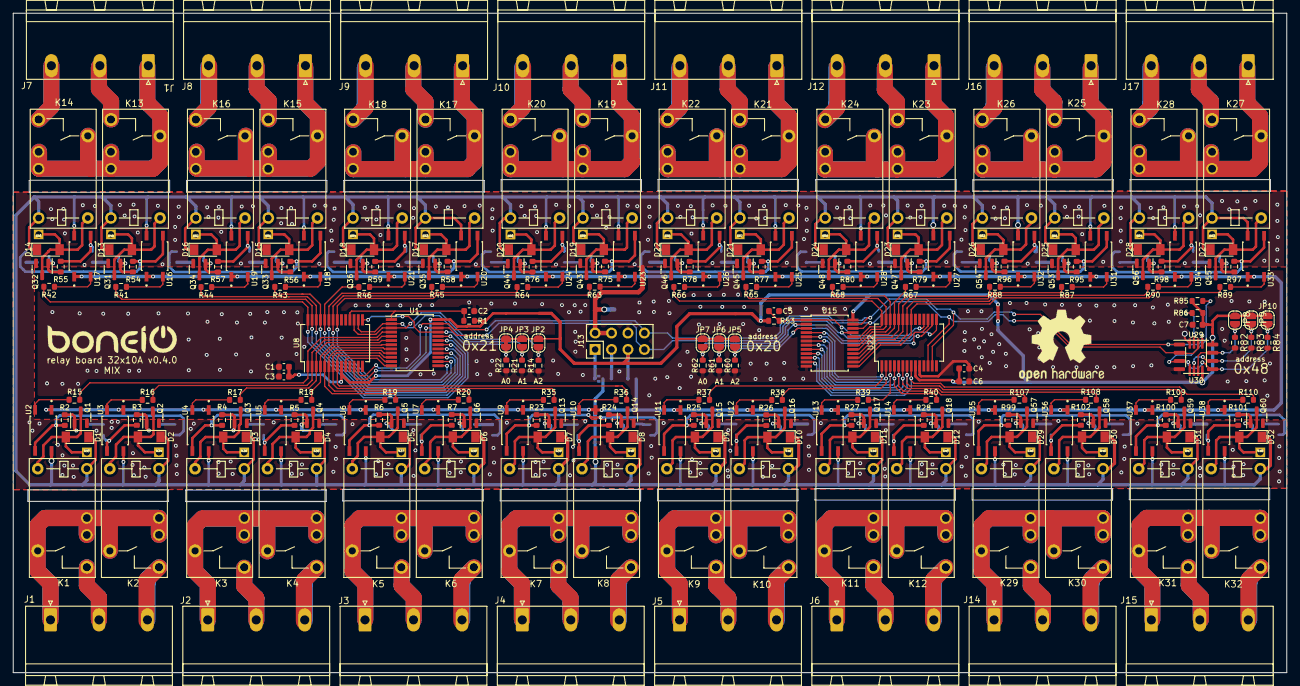
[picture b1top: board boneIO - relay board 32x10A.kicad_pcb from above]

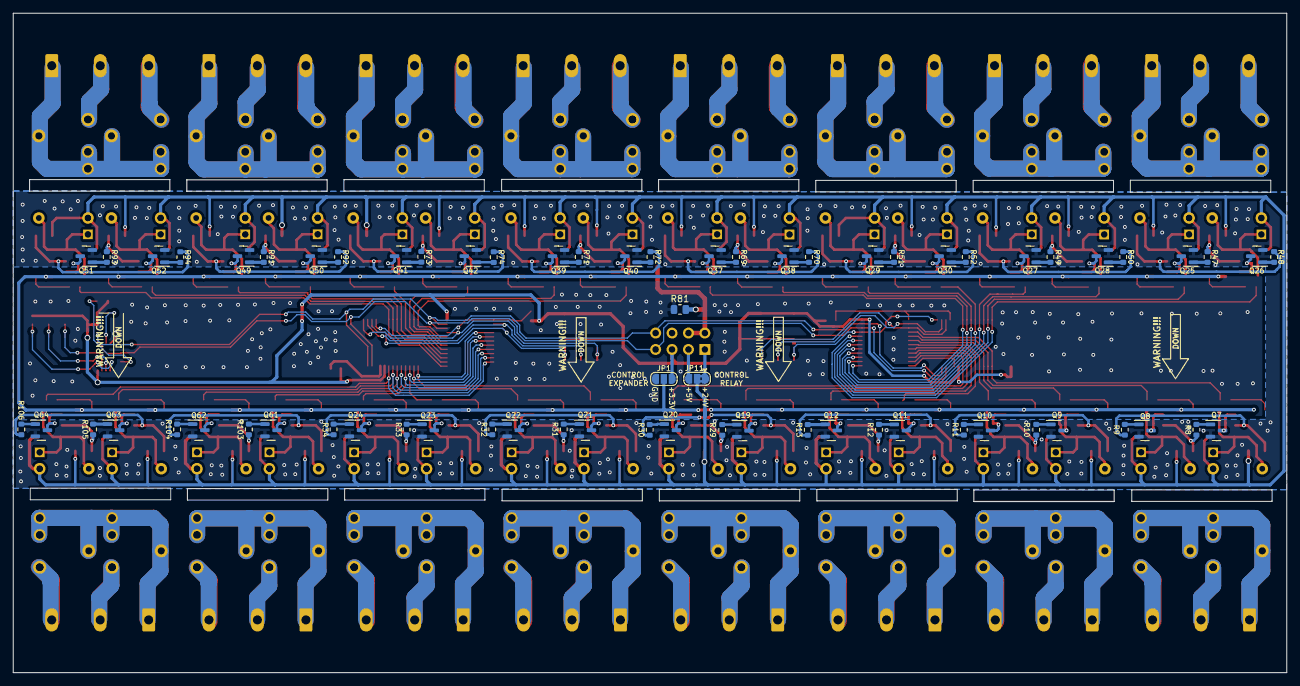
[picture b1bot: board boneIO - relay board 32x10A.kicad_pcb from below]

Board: 2 copper layers, 197.0 x 102.0 mm, 343 parts (67 on the bottom side), 262 nets.

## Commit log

2022-05-21 relay board v0.1
    new PCB
2022-05-22 relay board 32x10A v0.1
    Dodanie PCF8575
    Dodanie MCP23017
    Dodanie diody LL4148
2022-05-23 relay board 32x10A v0.1 (rev2)
    rozdzielenie GND
2022-05-26 v0.1
    dodanie dławika filtrujacego
2022-05-29 relay board 32x10A
    Final Version
2022-10-02 relay board v0.2
    Design changes:
    - addition of a jumper to set the i2c expander control
    - addition of PCF8575
2023-02-27 v0.4
